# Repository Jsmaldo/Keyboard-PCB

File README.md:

# Keyboard-PCB
 Keyboard PCB Including F1-F24 & arduino with attached encoders & OLED screen

http://www.keyboard-layout-editor.com/#/gists/6a09a1fa51d7aa38f726f7da2f79e6d3

Special parts include:
 https://www.aliexpress.us/item/3256804572132735.html?spm=a2g0o.order_list.order_list_main.4.7a7218022aEyPJ&gatewayAdapt=glo2usa&_randl_shipto=US
 https://www.digikey.com/en/products/detail/bourns-inc/PEC11L-4115F-S0020/4699168
 https://www.amazon.com/MakerFocus-Display-SSD1306-3-3V-5V-Arduino/dp/B079BN2J8V/ref=sr_1_5?crid=3C69TWMUGOQP3&keywords=oled+screen+i2c&qid=1669393383&sprefix=oled+screen+i2c%2Caps%2C93&sr=8-5

The OLED, slide pot, and rotary encoder will be controlled by a seperate processor, utilizing the deej project: https://github.com/omriharel/deej

Rotary encoder for selecting specific volume channel to adjust, and press-in to save slider value.
Motorized slide pot for adjusting specific channel volume
OLED for displaying current channel, and volume percentage.

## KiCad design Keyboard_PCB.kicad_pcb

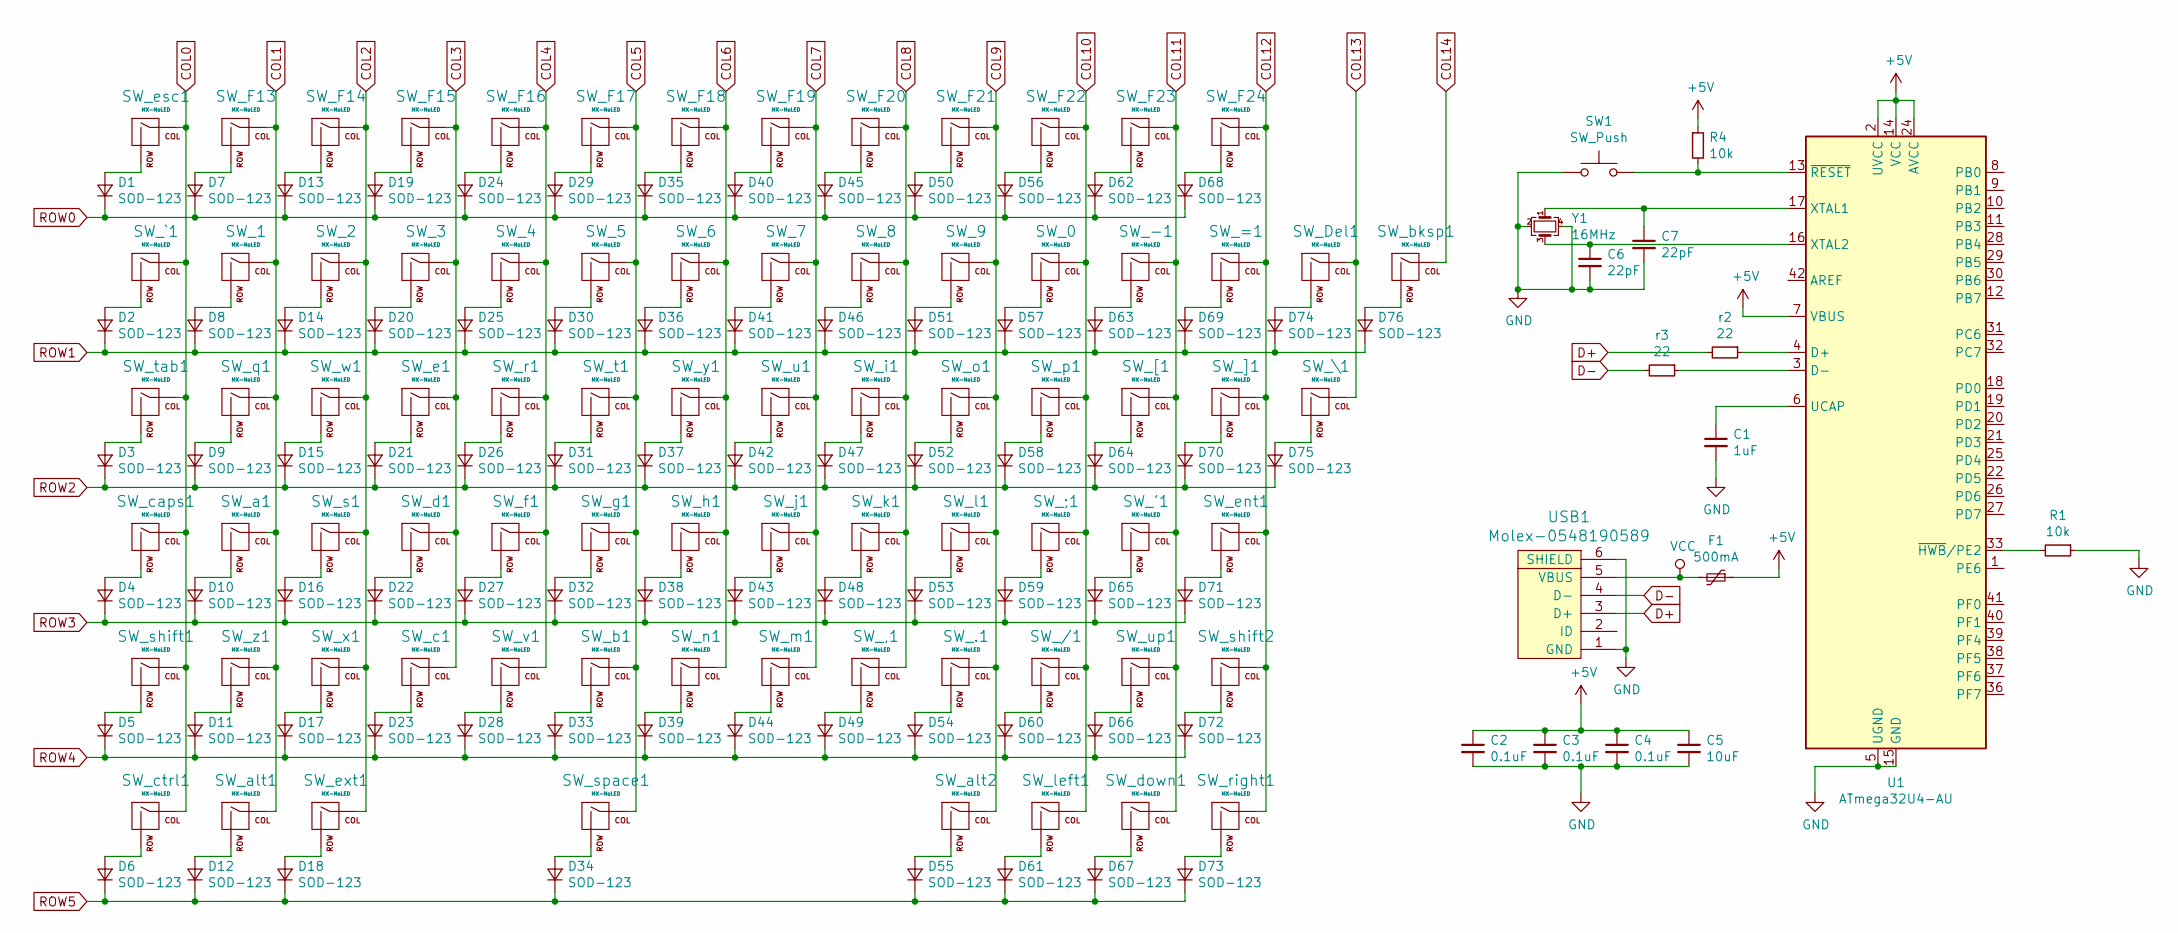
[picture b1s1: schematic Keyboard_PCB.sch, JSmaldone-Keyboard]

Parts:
C1: 1uF; C_0805_2012Metric
C2, C3, C4: 0.1uF; C_0805_2012Metric
C5: 10uF; C_0805_2012Metric
C6, C7: 22pF; C_0805_2012Metric
D1, D2, D3, D4, D5, D6, D7, D8, D9, D10, D11, D12, D13, D14, D15, D16, D17, D18, D19, D20, D21, D22, D23, D24, D25, D26, D27, D28, D29, D30, D31, D32, D33, D34, D35, D36, D37, D38, D39, D40, D41, D42, D43, D44, D45, D46, D47, D48, D49, D50, D51, D52, D53, D54, D55, D56, D57, D58, D59, D60, D61, D62, D63, D64, D65, D66, D67, D68, D69, D70, D71, D72, D73, D74, D75, D76: SOD-123; D_SOD-123
F1: 500mA; Fuse_1206_3216Metric
R1, R4: 10k; R_0805_2012Metric
SW1: SW_Push; SKQG-1155865
SW_0, SW_1, SW_2, SW_3, SW_4, SW_5, SW_6, SW_7, SW_8, SW_9, SW_.1: MX-NoLED; MX-1U-NoLED
SW_'1: MX-NoLED; MX-1U-NoLED
SW_,1: MX-NoLED; MX-1U-NoLED
SW_-1: MX-NoLED; MX-1U-NoLED
SW_/1: MX-NoLED; MX-1U-NoLED
SW_;1: MX-NoLED; MX-1U-NoLED
SW_=1: MX-NoLED; MX-1U-NoLED
SW_Del1: MX-NoLED; MX-1U-NoLED
SW_F13, SW_F14, SW_F15, SW_F16, SW_F17, SW_F18, SW_F19, SW_F20, SW_F21, SW_F22, SW_F23, SW_F24: MX-NoLED; MX-1U-NoLED
SW_[1: MX-NoLED; MX-1U-NoLED
SW_\1: MX-NoLED; MX-1.5U-NoLED
SW_]1: MX-NoLED; MX-1U-NoLED
SW_`1: MX-NoLED; MX-1U-NoLED
SW_a1: MX-NoLED; MX-1U-NoLED
SW_alt1, SW_alt2: MX-NoLED; MX-1U-NoLED
SW_b1: MX-NoLED; MX-1U-NoLED
SW_bksp1: MX-NoLED; MX-1U-NoLED
SW_c1: MX-NoLED; MX-1U-NoLED
SW_caps1: MX-NoLED; MX-1.75U-NoLED
SW_ctrl1: MX-NoLED; MX-1U-NoLED
SW_d1: MX-NoLED; MX-1U-NoLED
SW_down1: MX-NoLED; MX-1U-NoLED
SW_e1: MX-NoLED; MX-1U-NoLED
SW_ent1: MX-NoLED; MX-2.25U-NoLED
SW_esc1: MX-NoLED; MX-1U-NoLED
SW_ext1: MX-NoLED; MX-1U-NoLED
SW_f1: MX-NoLED; MX-1U-NoLED
SW_g1: MX-NoLED; MX-1U-NoLED
SW_h1: MX-NoLED; MX-1U-NoLED
SW_i1: MX-NoLED; MX-1U-NoLED
SW_j1: MX-NoLED; MX-1U-NoLED
SW_k1: MX-NoLED; MX-1U-NoLED
SW_l1: MX-NoLED; MX-1U-NoLED
SW_left1: MX-NoLED; MX-1U-NoLED
SW_m1: MX-NoLED; MX-1U-NoLED
SW_n1: MX-NoLED; MX-1U-NoLED
SW_o1: MX-NoLED; MX-1U-NoLED
SW_p1: MX-NoLED; MX-1U-NoLED
SW_q1: MX-NoLED; MX-1U-NoLED
SW_r1: MX-NoLED; MX-1U-NoLED
SW_right1: MX-NoLED; MX-1U-NoLED
SW_s1: MX-NoLED; MX-1U-NoLED
SW_shift1: MX-NoLED; MX-2.25U
SW_shift2: MX-NoLED; MX-1.75U
SW_space1: MX-NoLED; MX-7U
SW_t1: MX-NoLED; MX-1U-NoLED
SW_tab1: MX-NoLED; MX-1.5U-NoLED
SW_u1: MX-NoLED; MX-1U-NoLED
SW_up1: MX-NoLED; MX-1U-NoLED
SW_v1: MX-NoLED; MX-1U-NoLED
SW_w1: MX-NoLED; MX-1U-NoLED
SW_x1: MX-NoLED; MX-1U-NoLED
SW_y1: MX-NoLED; MX-1U-NoLED
SW_z1: MX-NoLED; MX-1U-NoLED
U1: ATmega32U4-AU; TQFP-44_10x10mm_P0.8mm
USB1: Molex-0548190589
Y1: 16MHz; Crystal_SMD_3225-4Pin_3.2x2.5mm
r2, r3: 22; R_0805_2012Metric

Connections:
+5V: C2.1, C3.1, C4.1, C5.1, F1.1, R4.1, U1.2 (UVCC), U1.7 (VBUS), U1.14 (VCC), U1.24 (AVCC), U1.34 (VCC), U1.44 (AVCC)
COL0: SW_`1.1 (COL), SW_caps1.1 (COL), SW_ctrl1.1 (COL), SW_esc1.1 (COL), SW_shift1.1 (COL), SW_tab1.1 (COL)
COL1: SW_1.1 (COL), SW_F13.1 (COL), SW_a1.1 (COL), SW_alt1.1 (COL), SW_q1.1 (COL), SW_z1.1 (COL)
COL2: SW_2.1 (COL), SW_F14.1 (COL), SW_ext1.1 (COL), SW_s1.1 (COL), SW_w1.1 (COL), SW_x1.1 (COL)
COL3: SW_3.1 (COL), SW_F15.1 (COL), SW_c1.1 (COL), SW_d1.1 (COL), SW_e1.1 (COL)
COL4: SW_4.1 (COL), SW_F16.1 (COL), SW_f1.1 (COL), SW_r1.1 (COL), SW_v1.1 (COL)
COL5: SW_5.1 (COL), SW_F17.1 (COL), SW_b1.1 (COL), SW_g1.1 (COL), SW_space1.1 (COL), SW_t1.1 (COL)
COL6: SW_6.1 (COL), SW_F18.1 (COL), SW_h1.1 (COL), SW_n1.1 (COL), SW_y1.1 (COL)
COL7: SW_7.1 (COL), SW_F19.1 (COL), SW_j1.1 (COL), SW_m1.1 (COL), SW_u1.1 (COL)
COL8: SW_8.1 (COL), SW_,1.1 (COL), SW_F20.1 (COL), SW_i1.1 (COL), SW_k1.1 (COL)
COL9: SW_9.1 (COL), SW_.1.1 (COL), SW_F21.1 (COL), SW_alt2.1 (COL), SW_l1.1 (COL), SW_o1.1 (COL)
COL10: SW_0.1 (COL), SW_/1.1 (COL), SW_;1.1 (COL), SW_F22.1 (COL), SW_left1.1 (COL), SW_p1.1 (COL)
COL11: SW_'1.1 (COL), SW_-1.1 (COL), SW_F23.1 (COL), SW_[1.1 (COL), SW_down1.1 (COL), SW_up1.1 (COL)
COL12: SW_=1.1 (COL), SW_F24.1 (COL), SW_]1.1 (COL), SW_ent1.1 (COL), SW_right1.1 (COL), SW_shift2.1 (COL)
COL13: SW_Del1.1 (COL), SW_\1.1 (COL)
COL14: SW_bksp1.1 (COL)
D+: USB1.3 (D+), r2.2
D-: USB1.4 (D-), r3.2
GND: C1.2, C2.2, C3.2, C4.2, C5.2, C6.2, C7.2, R1.1, SW1.1, U1.5 (UGND), U1.15 (GND), U1.23 (GND), U1.35 (GND), U1.43 (GND), USB1.1 (GND), USB1.6 (SHIELD), Y1.2, Y1.4
unnamed: C1.1, U1.6 (UCAP)
unnamed: C6.1, U1.16 (XTAL2), Y1.3
unnamed: C7.1, U1.17 (XTAL1), Y1.1
unnamed: D1.2 (A), SW_esc1.2 (ROW)
unnamed: D2.2 (A), SW_`1.2 (ROW)
unnamed: D3.2 (A), SW_tab1.2 (ROW)
unnamed: D4.2 (A), SW_caps1.2 (ROW)
unnamed: D5.2 (A), SW_shift1.2 (ROW)
unnamed: D6.2 (A), SW_ctrl1.2 (ROW)
unnamed: D7.2 (A), SW_F13.2 (ROW)
unnamed: D8.2 (A), SW_1.2 (ROW)
unnamed: D9.2 (A), SW_q1.2 (ROW)
unnamed: D10.2 (A), SW_a1.2 (ROW)
unnamed: D11.2 (A), SW_z1.2 (ROW)
unnamed: D12.2 (A), SW_alt1.2 (ROW)
unnamed: D13.2 (A), SW_F14.2 (ROW)
unnamed: D14.2 (A), SW_2.2 (ROW)
unnamed: D15.2 (A), SW_w1.2 (ROW)
unnamed: D16.2 (A), SW_s1.2 (ROW)
unnamed: D17.2 (A), SW_x1.2 (ROW)
unnamed: D18.2 (A), SW_ext1.2 (ROW)
unnamed: D19.2 (A), SW_F15.2 (ROW)
unnamed: D20.2 (A), SW_3.2 (ROW)
unnamed: D21.2 (A), SW_e1.2 (ROW)
unnamed: D22.2 (A), SW_d1.2 (ROW)
unnamed: D23.2 (A), SW_c1.2 (ROW)
unnamed: D24.2 (A), SW_F16.2 (ROW)
unnamed: D25.2 (A), SW_4.2 (ROW)
unnamed: D26.2 (A), SW_r1.2 (ROW)
unnamed: D27.2 (A), SW_f1.2 (ROW)
unnamed: D28.2 (A), SW_v1.2 (ROW)
unnamed: D29.2 (A), SW_F17.2 (ROW)
unnamed: D30.2 (A), SW_5.2 (ROW)
unnamed: D31.2 (A), SW_t1.2 (ROW)
unnamed: D32.2 (A), SW_g1.2 (ROW)
unnamed: D33.2 (A), SW_b1.2 (ROW)
unnamed: D34.2 (A), SW_space1.2 (ROW)
unnamed: D35.2 (A), SW_F18.2 (ROW)
unnamed: D36.2 (A), SW_6.2 (ROW)
unnamed: D37.2 (A), SW_y1.2 (ROW)
unnamed: D38.2 (A), SW_h1.2 (ROW)
unnamed: D39.2 (A), SW_n1.2 (ROW)
unnamed: D40.2 (A), SW_F19.2 (ROW)
unnamed: D41.2 (A), SW_7.2 (ROW)
unnamed: D42.2 (A), SW_u1.2 (ROW)
unnamed: D43.2 (A), SW_j1.2 (ROW)
unnamed: D44.2 (A), SW_m1.2 (ROW)
unnamed: D45.2 (A), SW_F20.2 (ROW)
unnamed: D46.2 (A), SW_8.2 (ROW)
unnamed: D47.2 (A), SW_i1.2 (ROW)
unnamed: D48.2 (A), SW_k1.2 (ROW)
unnamed: D49.2 (A), SW_,1.2 (ROW)
unnamed: D50.2 (A), SW_F21.2 (ROW)
unnamed: D51.2 (A), SW_9.2 (ROW)
unnamed: D52.2 (A), SW_o1.2 (ROW)
unnamed: D53.2 (A), SW_l1.2 (ROW)
unnamed: D54.2 (A), SW_.1.2 (ROW)
unnamed: D55.2 (A), SW_alt2.2 (ROW)
unnamed: D56.2 (A), SW_F22.2 (ROW)
unnamed: D57.2 (A), SW_0.2 (ROW)
unnamed: D58.2 (A), SW_p1.2 (ROW)
unnamed: D59.2 (A), SW_;1.2 (ROW)
unnamed: D60.2 (A), SW_/1.2 (ROW)
unnamed: D61.2 (A), SW_left1.2 (ROW)
unnamed: D62.2 (A), SW_F23.2 (ROW)
unnamed: D63.2 (A), SW_-1.2 (ROW)
unnamed: D64.2 (A), SW_[1.2 (ROW)
unnamed: D65.2 (A), SW_'1.2 (ROW)
unnamed: D66.2 (A), SW_up1.2 (ROW)
unnamed: D67.2 (A), SW_down1.2 (ROW)
unnamed: D68.2 (A), SW_F24.2 (ROW)
unnamed: D69.2 (A), SW_=1.2 (ROW)
unnamed: D70.2 (A), SW_]1.2 (ROW)
unnamed: D71.2 (A), SW_ent1.2 (ROW)
unnamed: D72.2 (A), SW_shift2.2 (ROW)
unnamed: D73.2 (A), SW_right1.2 (ROW)
unnamed: D74.2 (A), SW_Del1.2 (ROW)
unnamed: D75.2 (A), SW_\1.2 (ROW)
unnamed: D76.2 (A), SW_bksp1.2 (ROW)
unnamed: R1.2, U1.33 (~HWB~/PE2)
unnamed: R4.2, SW1.2, U1.13 (~RESET)
unnamed: U1.3 (D-), r3.1
unnamed: U1.4 (D+), r2.1
ROW0: D1.1 (K), D7.1 (K), D13.1 (K), D19.1 (K), D24.1 (K), D29.1 (K), D35.1 (K), D40.1 (K), D45.1 (K), D50.1 (K), D56.1 (K), D62.1 (K), D68.1 (K)
ROW1: D2.1 (K), D8.1 (K), D14.1 (K), D20.1 (K), D25.1 (K), D30.1 (K), D36.1 (K), D41.1 (K), D46.1 (K), D51.1 (K), D57.1 (K), D63.1 (K), D69.1 (K), D74.1 (K), D76.1 (K)
ROW2: D3.1 (K), D9.1 (K), D15.1 (K), D21.1 (K), D26.1 (K), D31.1 (K), D37.1 (K), D42.1 (K), D47.1 (K), D52.1 (K), D58.1 (K), D64.1 (K), D70.1 (K), D75.1 (K)
ROW3: D4.1 (K), D10.1 (K), D16.1 (K), D22.1 (K), D27.1 (K), D32.1 (K), D38.1 (K), D43.1 (K), D48.1 (K), D53.1 (K), D59.1 (K), D65.1 (K), D71.1 (K)
ROW4: D5.1 (K), D11.1 (K), D17.1 (K), D23.1 (K), D28.1 (K), D33.1 (K), D39.1 (K), D44.1 (K), D49.1 (K), D54.1 (K), D60.1 (K), D66.1 (K), D72.1 (K)
ROW5: D6.1 (K), D12.1 (K), D18.1 (K), D34.1 (K), D55.1 (K), D61.1 (K), D67.1 (K), D73.1 (K)
VCC: F1.2, USB1.5 (VBUS)

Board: 2 copper layers, 171 parts (92 on the bottom side), 108 nets, no tracks yet.

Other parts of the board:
OL1: OLED; OLED_v2
R2: PSM60-081A-103B2
S1: PEC11-4215F-S24; PEC11R-4xxx-Sxxxx

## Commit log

2022-11-21 New blank project
2022-11-21 Add submodules
2022-11-21 Create fp-info-cache
2022-11-21 Schematic sample populated
2022-11-21 PCB update
    some progress on pcb
2022-11-25 keyboard laid out in schematic
2022-11-25 link deej project
2022-11-26 updated PCB
2022-11-26 added parts
    added OLED, Slidepot, and Rotary encoder to sch and pcb
2022-12-01 new slide pot
    Original slide pot wont work sadly, bringing in a different design from aliexpress
2022-12-01 test rotary encoder with OLED
    testing rotary encoder and OLED circuit
2022-12-03 cleaning up folders
2022-12-05 folder & code updates
    putting pcb files in a new folder broke some library paths. Working on incorporating analog slider.
2022-12-11 add controls for H bridge
    utilizing the TB6612FNG for now
2022-12-28 clean up files, put libraries in seperate repo
2022-12-29 adding components
2023-01-03 Schematic Organization
    -separated schematic into stages / sections
2023-02-23 added basic firmware and layout info
2023-02-23 updated PCB layout
    assigned col/row pins and organized keys according to keymap

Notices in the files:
parts and their libraries:
Copyright 2021 Accelerated Designs. All rights reserved.
